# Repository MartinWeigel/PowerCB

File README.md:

# PowerCB

PowerCB is a small PCB to power a breadboard with 3.3V. It has a small footprint to avoid blocking pins on the breadboard. The measurements fit an ELEGOO breadboard, but should work with other brands as well. It can be either used on the side of the breadboard to power one side only *or* in the middle to bridge all power lines. The board can be powered through USB-C or the two mounting holes, e.g. by connecting it to a power supply. It is based on a [TPS73633](http://www.ti.com/product/TPS73633-EP) low-dropout (LDO) linear voltage regulator. The optional 0805-capacitor pads can be used for additional bypass capacitors.

This board was designed using [KiCad 6.0](http://www.kicad.org).

## Design

## BOM
Reference | Part        | Description
--------- | ----------- | ---
U1        | <a href="https://www.mouser.de/ProductDetail/595-TPS73633DBVR/">TPS73633DBVR</a> | 3.3V LDO Voltage Regulator
U2        | <a href="https://www.mouser.de/ProductDetail/CUI-Devices/UJC-HP-3-SMT-TR?qs=vmHwEFxEFR%252BLRSV%252Bufrn1g%3D%3D">UJC-HP-3-SMT-TR</a> | USB Type C receptacle
R1        | 0805 Resistor     | Resistor for LED (680 Ω)
R2        | 0805 Resistor     | USB-C pulldown resistor (5.1 kΩ)
R3        | 0805 Resistor     | USB-C pulldown resistor (5.1 kΩ)
D1        | 0805 LED          | Power-on status
C1-6      | 0805 Capacitor    | Optional capacitors
J6-9      | Male Pin Header   | 2.54mm spacing

## License
<br />This work is licensed under a <a rel="license" href="http://creativecommons.org/licenses/by/4.0/">Creative Commons Attribution 4.0 International License</a>.

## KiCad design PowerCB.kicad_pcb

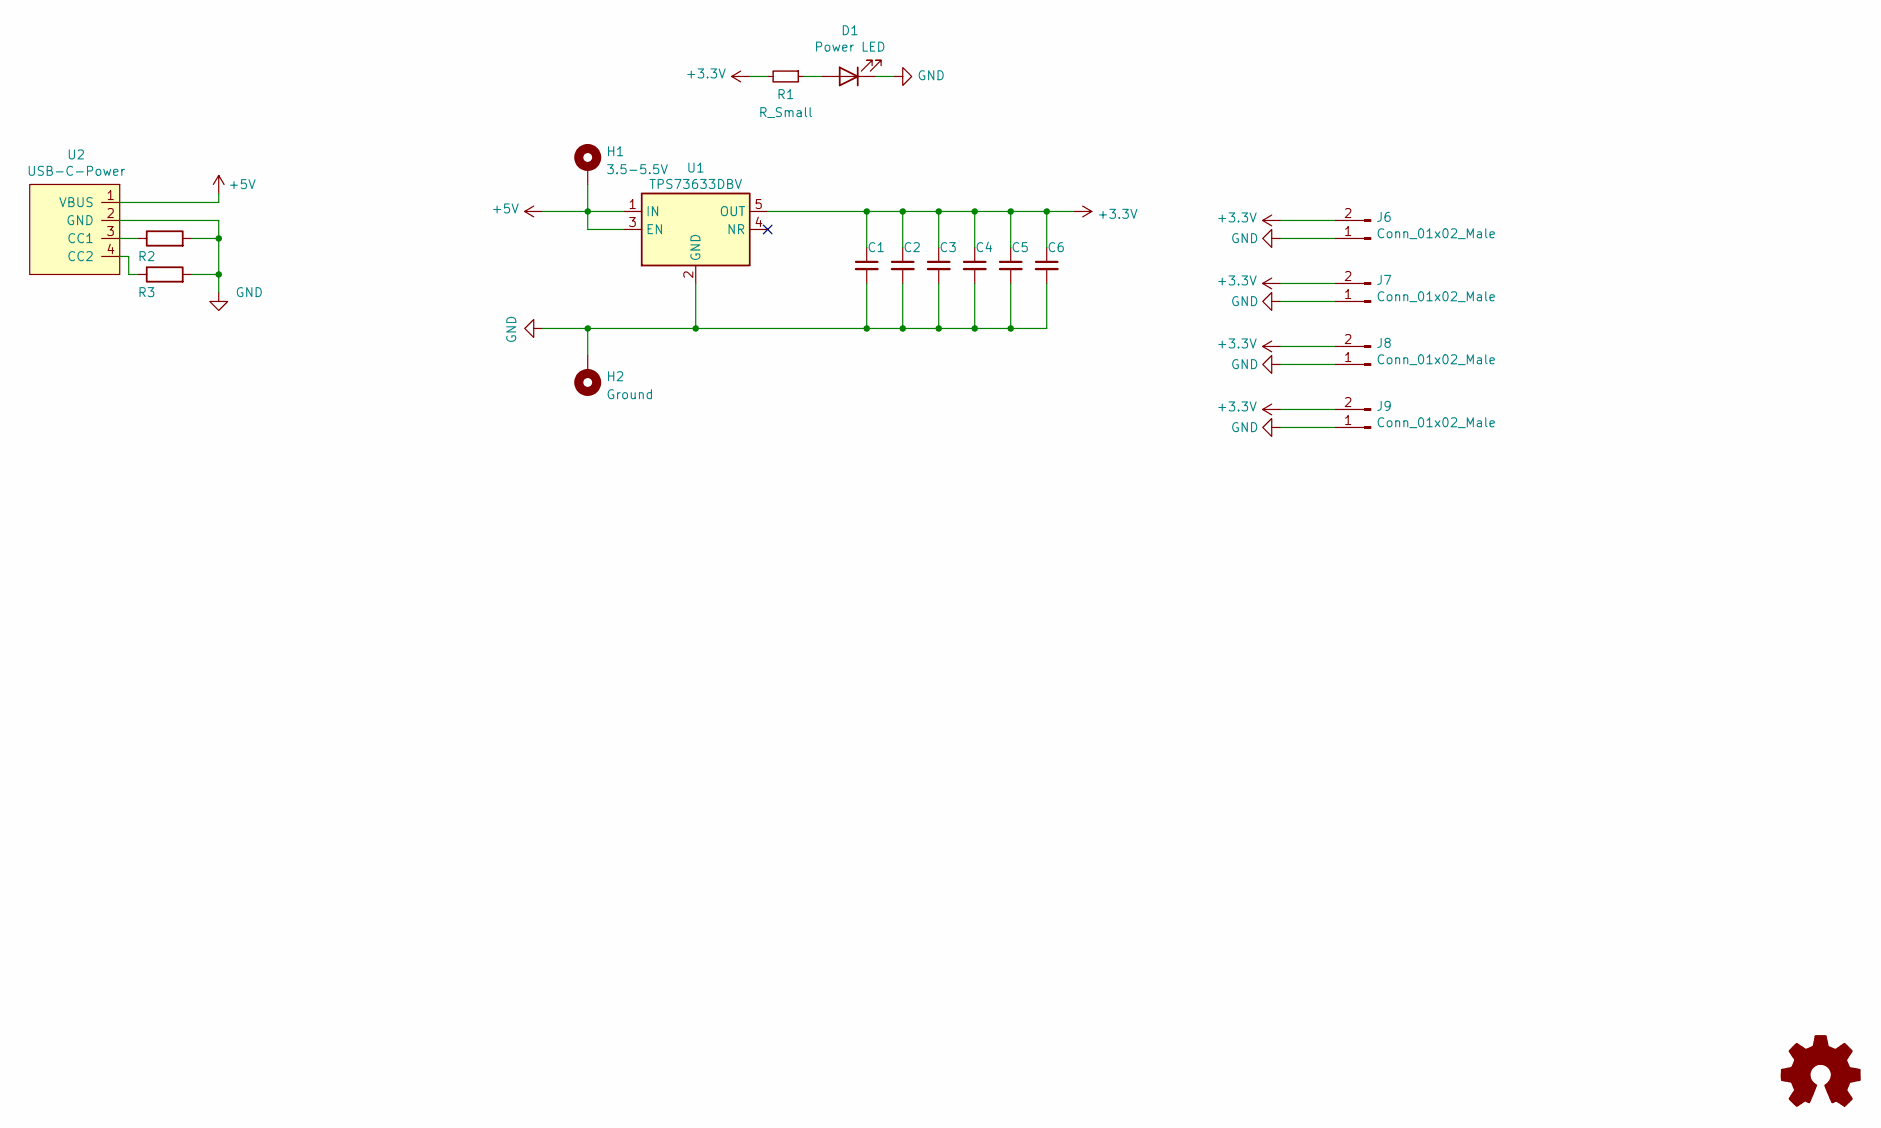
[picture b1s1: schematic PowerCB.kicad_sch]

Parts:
C1, C2, C3, C4, C5, C6: C_Small; C_0805_2012Metric_Pad1.15x1.40mm_HandSolder
D1: Power LED; LED_0805_2012Metric_Pad1.15x1.40mm_HandSolder
H1: 3.5-5.5V; MountingHole_3.2mm_M3_DIN965_Pad
H2: Ground; MountingHole_3.2mm_M3_DIN965_Pad
J6, J7, J8, J9: Conn_01x02_Male; PinHeader_1x02_P2.54mm_Vertical
R1: R_Small; R_0805_2012Metric_Pad1.15x1.40mm_HandSolder
R2, R3: (no value)
U1: TPS73633DBV; SOT-23-5_HandSoldering
U2: USB-C-Power; UJC-HP-3-SMT-TR

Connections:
+3V3: C1.1, C2.1, C3.1, C4.1, C5.1, C6.1, J6.2, J7.2, J8.2, J9.2, R1.2, U1.5 (OUT)
+5V: H1.1, U1.1 (IN), U1.3 (EN), U2.1 (VBUS)
GND: C1.2, C2.2, C3.2, C4.2, C5.2, C6.2, D1.1 (K), H2.1, J6.1, J7.1, J8.1, J9.1, R2.2, R3.2, U1.2 (GND), U2.2 (GND)
unnamed: D1.2 (A), R1.1
unnamed: R2.1, U2.3 (CC1)
unnamed: R3.1, U2.4 (CC2)

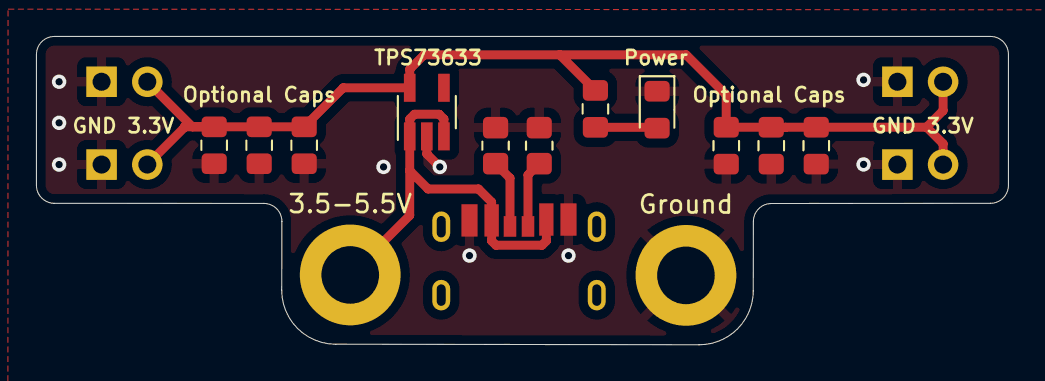
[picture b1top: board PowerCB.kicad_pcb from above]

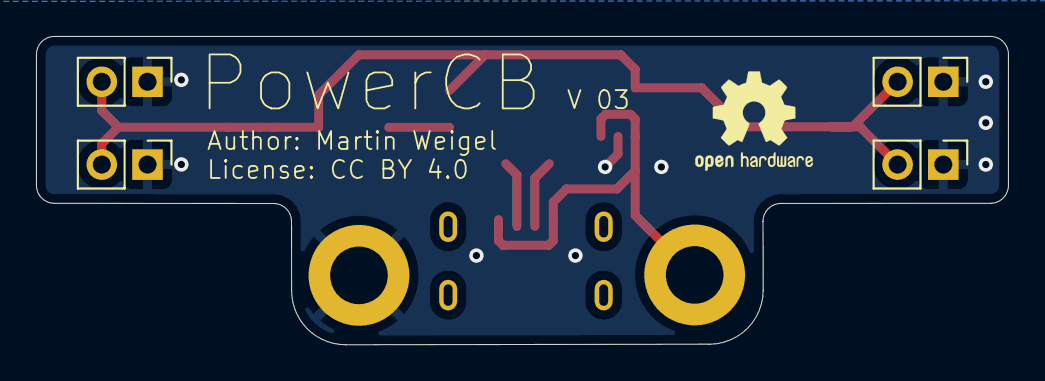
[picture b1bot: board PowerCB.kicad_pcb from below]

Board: 2 copper layers, 54.0 x 17.1 mm, 18 parts (4 on the bottom side), 6 nets.

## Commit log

2019-12-14 PowerCB V01
2020-12-21 feat: USB-C instead of Micro-USB connector
2022-03-26 chore: convert to KiCad 6 file formats
2022-03-26 feat: M3 instead of M2 mounting holes
2022-04-01 fix: missing USB-C CC pulldown resistors
2022-04-01 feat: OSHW logo
2022-04-01 fix: update README

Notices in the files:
PowerCB.kicad_pcb:
https://creativecommons.org/licenses/by/4.0
License: CC BY 4.0
